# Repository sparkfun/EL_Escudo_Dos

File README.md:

SparkFun EL Escudo Dos
========================================

[*SparkFun EL Escudo Dos (COM-10878)*](https://www.sparkfun.com/products/10878)

The SparkFun EL Escudo Dos is an Arduino shield for controlling up to eight strands of electroluminescent wire. 
EL wire is flexible plastic cord that glows brightly when high-voltage AC is applied to it.
The El Escudo Dos contains circuitry to safely switch high-voltage AC on and off, allowing you to create animated displays or whatever else your imagination can come up with.

Repository Contents
-------------------

* **/Firmware** - Example code 
* **/Hardware** - Eagle design files (.brd, .sch)
* **/Production** - Production panel files (.brd)

Documentation
--------------
* **[Hookup Guide](https://www.sparkfun.com/tutorials/353)** - Basic hookup guide for the EL Escudo Dos.
* **[SparkFun Fritzing repo](https://github.com/sparkfun/Fritzing_Parts)** - Fritzing diagrams for SparkFun products.
* **[SparkFun 3D Model repo](https://github.com/sparkfun/3D_Models)** - 3D models of SparkFun products. 

License Information
-------------------
This product is _**open source**_! 

The **hardware** is released under [Creative Commons ShareAlike 4.0 International](https://creativecommons.org/licenses/by-sa/4.0/).

The **code** is beerware; if you see me (or any other SparkFun employee) at the local, and you've found our code helpful, please buy us a round!

Please use, reuse, and modify these files as you see fit. Please maintain attribution to SparkFun Electronics and release anything derivative under the same license.

Distributed as-is; no warranty is given.

- Your friends at SparkFun.

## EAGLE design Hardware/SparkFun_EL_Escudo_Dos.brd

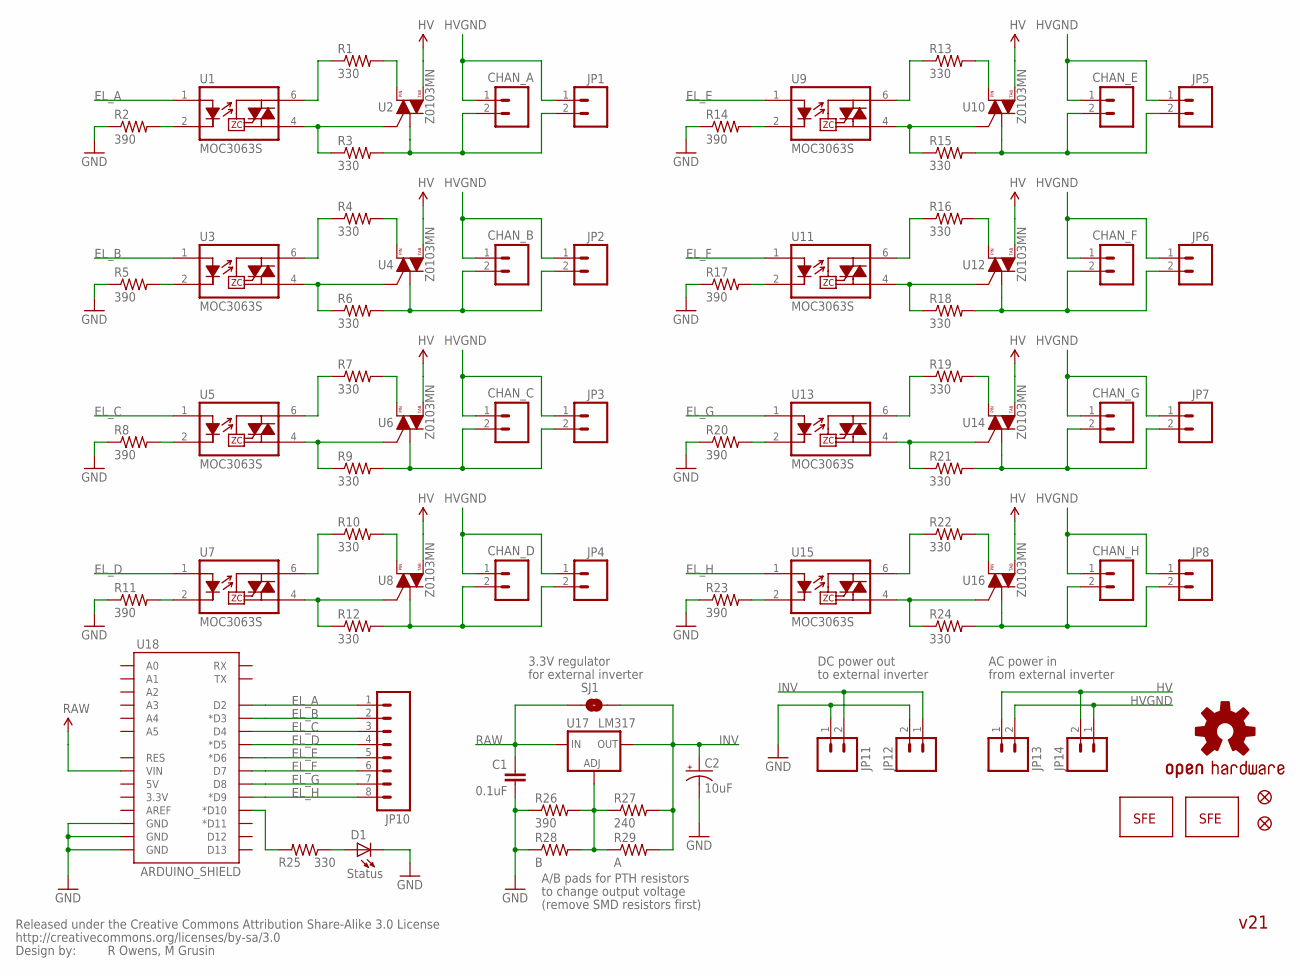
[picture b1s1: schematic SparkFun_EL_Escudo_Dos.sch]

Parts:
C1: 0.1uF; 0603-CAP
C2: 10uF; EIA3216
CHAN_A: M02-JST-2MM-SMT; JST-2-SMD
CHAN_B: M02-JST-2MM-SMT; JST-2-SMD
CHAN_C: M02-JST-2MM-SMT; JST-2-SMD
CHAN_D: M02-JST-2MM-SMT; JST-2-SMD
CHAN_E: M02-JST-2MM-SMT; JST-2-SMD
CHAN_F: M02-JST-2MM-SMT; JST-2-SMD
CHAN_G: M02-JST-2MM-SMT; JST-2-SMD
CHAN_H: M02-JST-2MM-SMT; JST-2-SMD
D1: Status; LED-0603
JP1, JP2, JP3, JP4, JP5, JP6, JP7, JP8, JP12, JP13: M02PTH; 1X02
JP9, JP15: LOGO-SFENEW; SFE-NEW-WEBLOGO
JP10: M081X08; 1X08
JP11, JP14: M02-JST-2MM-SMT; JST-2-SMD
JP16, JP17: FIDUCIALUFIDUCIAL; MICRO-FIDUCIAL
R1, R3, R4, R6, R7, R9, R10, R12, R13, R15, R16, R18, R19, R21, R22, R24, R25: 330; 0603-RES
R2, R5, R8, R11, R14, R17, R20, R23, R26: 390; 0603-RES
R27: 240; 0603-RES
R28: B; AXIAL-0.4
R29: A; AXIAL-0.4
SJ1: SOLDERJUMPERNO; SJ_2S-NO
U1, U3, U5, U7, U9, U11, U13, U15: MOC3063S; DIP8SMD
U2, U4, U6, U8, U10, U12, U14, U16: Z0103MN; SOT223
U17: LM317; V-REG_DPACK
U18: ARDUINO_SHIELD; DUEMILANOVE_SHIELD_NOLABELS
U$4: CREATIVE_COMMONS
U$5: OSHW-LOGOS; OSHW-LOGO-S

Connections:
EL_A: JP10.1, U1.1 (A), U18.D2
EL_B: JP10.2, U3.1 (A), U18.D3 (*D3)
EL_C: JP10.3, U5.1 (A), U18.D4
EL_D: JP10.4, U7.1 (A), U18.D5 (*D5)
EL_E: JP10.5, U9.1 (A), U18.D6 (*D6)
EL_F: JP10.6, U11.1 (A), U18.D7
EL_G: JP10.7, U13.1 (A), U18.D8
EL_H: JP10.8, U15.1 (A), U18.D9 (*D9)
GND: C1.2, C2.C (-), D1.C, JP11.1, JP12.2, R2.1, R5.1, R8.1, R11.1, R14.1, R17.1, R20.1, R23.1, R26.1, R28.P$1 (1), U18.GND@0 (GND), U18.GND@1 (GND), U18.GND@2 (GND)
HV: JP13.1, JP14.2, U2.4 (T2), U4.4 (T2), U6.4 (T2), U8.4 (T2), U10.4 (T2), U12.4 (T2), U14.4 (T2), U16.4 (T2)
HVGND: CHAN_A.1, CHAN_B.1, CHAN_C.1, CHAN_D.1, CHAN_E.1, CHAN_F.1, CHAN_G.1, CHAN_H.1, JP1.1, JP2.1, JP3.1, JP4.1, JP5.1, JP6.1, JP7.1, JP8.1, JP13.2, JP14.1
INV: C2.A (+), JP11.2, JP12.1, R27.2, R29.P$2 (2), SJ1.2, U17.4 (OUT)
unnamed: R2.2, U1.2 (K)
unnamed: R26.2, R27.1, R28.P$2 (2), R29.P$1 (1), U17.1 (ADJ)
unnamed: R1.1, U1.6 (T1)
unnamed: R25.2, U18.D10 (*D10)
unnamed: R6.1, U3.4 (T2), U4.3 (G)
unnamed: R5.2, U3.2 (K)
unnamed: R4.1, U3.6 (T1)
unnamed: CHAN_B.2, JP2.2, R6.2, U4.1 (T1)
unnamed: R1.2, U2.2 (T2)
unnamed: R9.1, U5.4 (T2), U6.3 (G)
unnamed: R8.2, U5.2 (K)
unnamed: R7.1, U5.6 (T1)
unnamed: CHAN_C.2, JP3.2, R9.2, U6.1 (T1)
unnamed: D1.A, R25.1
unnamed: R4.2, U4.2 (T2)
unnamed: R12.1, U7.4 (T2), U8.3 (G)
unnamed: R11.2, U7.2 (K)
unnamed: R10.1, U7.6 (T1)
unnamed: CHAN_D.2, JP4.2, R12.2, U8.1 (T1)
unnamed: R7.2, U6.2 (T2)
unnamed: CHAN_A.2, JP1.2, R3.2, U2.1 (T1)
unnamed: R15.1, U9.4 (T2), U10.3 (G)
unnamed: R14.2, U9.2 (K)
unnamed: R13.1, U9.6 (T1)
unnamed: CHAN_E.2, JP5.2, R15.2, U10.1 (T1)
unnamed: R10.2, U8.2 (T2)
unnamed: R18.1, U11.4 (T2), U12.3 (G)
unnamed: R17.2, U11.2 (K)
unnamed: R16.1, U11.6 (T1)
unnamed: CHAN_F.2, JP6.2, R18.2, U12.1 (T1)
unnamed: R13.2, U10.2 (T2)
unnamed: R21.1, U13.4 (T2), U14.3 (G)
unnamed: R20.2, U13.2 (K)
unnamed: R19.1, U13.6 (T1)
unnamed: CHAN_G.2, JP7.2, R21.2, U14.1 (T1)
unnamed: R16.2, U12.2 (T2)
unnamed: R24.1, U15.4 (T2), U16.3 (G)
unnamed: R23.2, U15.2 (K)
unnamed: R22.1, U15.6 (T1)
unnamed: CHAN_H.2, JP8.2, R24.2, U16.1 (T1)
unnamed: R19.2, U14.2 (T2)
unnamed: R22.2, U16.2 (T2)
unnamed: R3.1, U1.4 (T2), U2.3 (G)
RAW: C1.1, SJ1.1, U17.3 (IN), U18.VIN

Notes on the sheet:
AC power in
from external inverter
DC power out
to external inverter
3.3V regulator
R Owens, M Grusin
for external inverter
A/B pads for PTH resistors
to change output voltage
(remove SMD resistors first)
v21

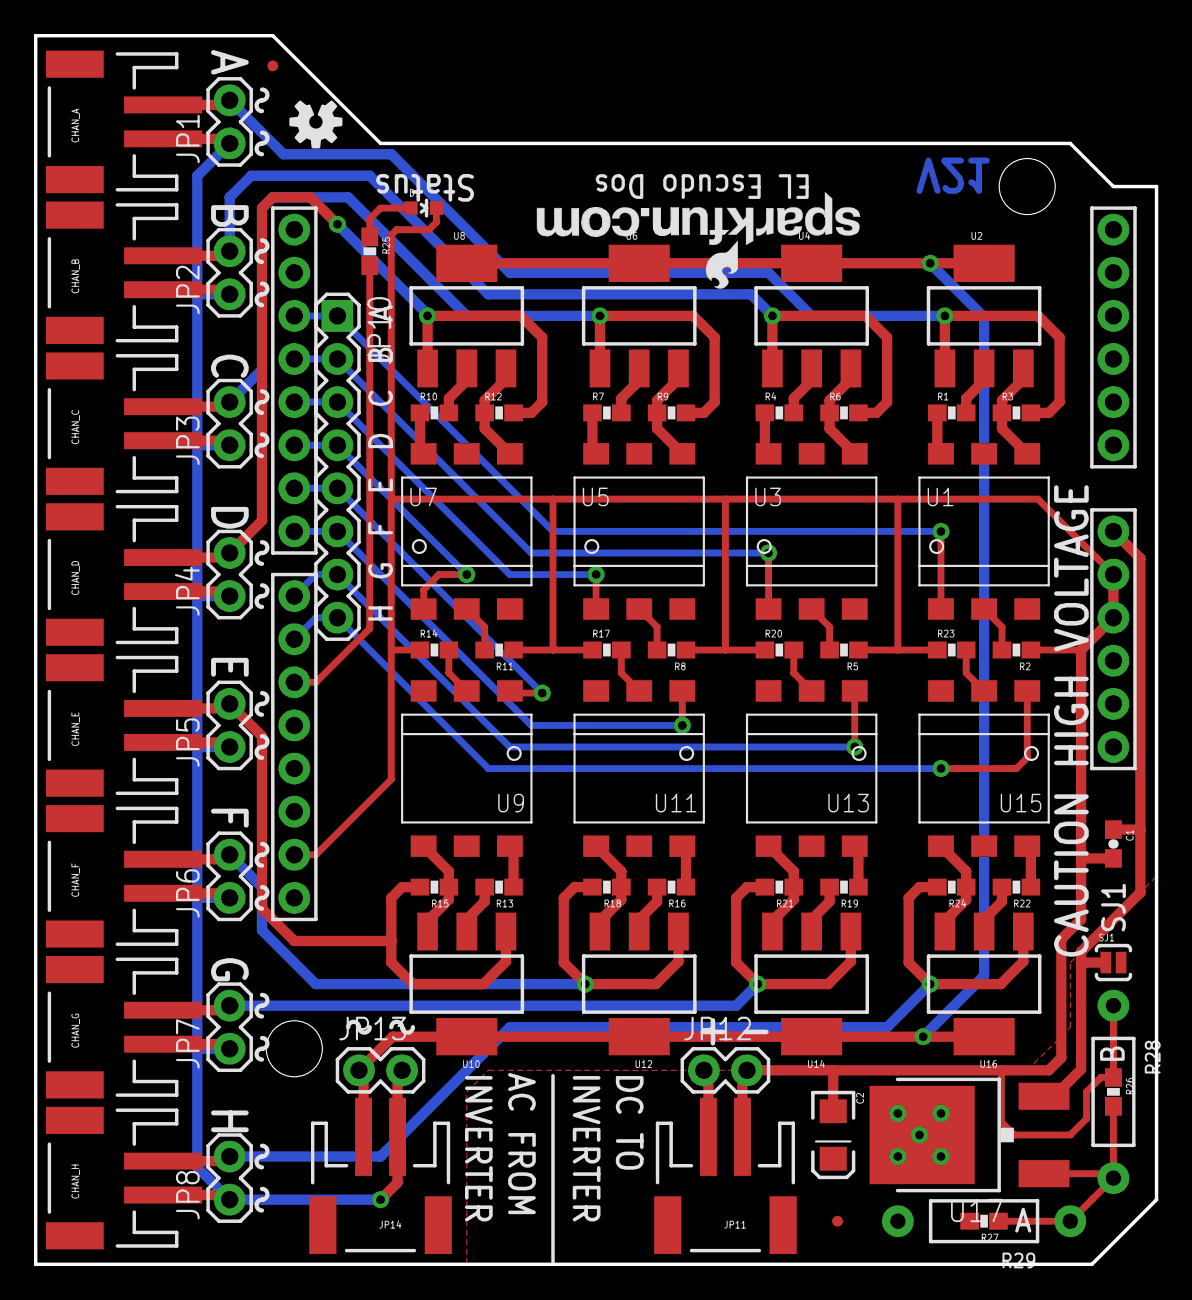
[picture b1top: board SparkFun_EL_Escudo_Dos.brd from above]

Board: 2 copper layers, 66.0 x 72.4 mm, 78 parts (1 on the bottom side), 56 nets.

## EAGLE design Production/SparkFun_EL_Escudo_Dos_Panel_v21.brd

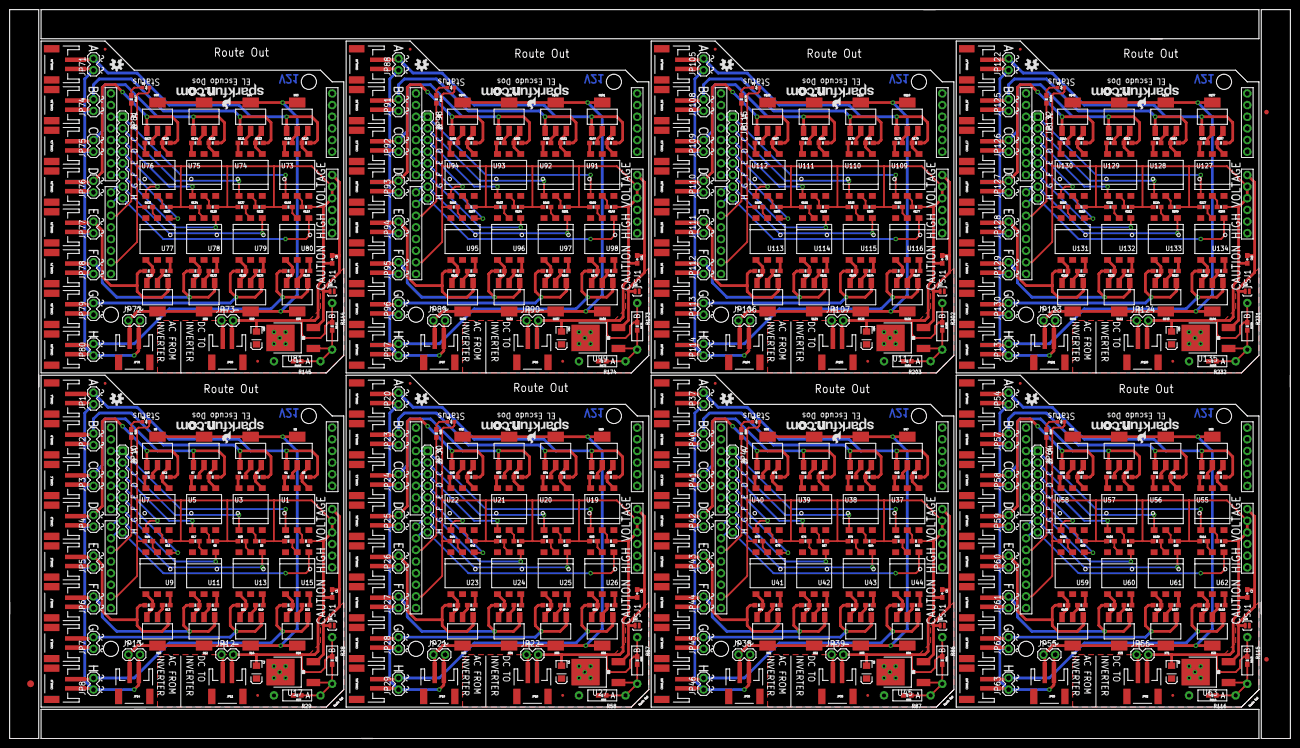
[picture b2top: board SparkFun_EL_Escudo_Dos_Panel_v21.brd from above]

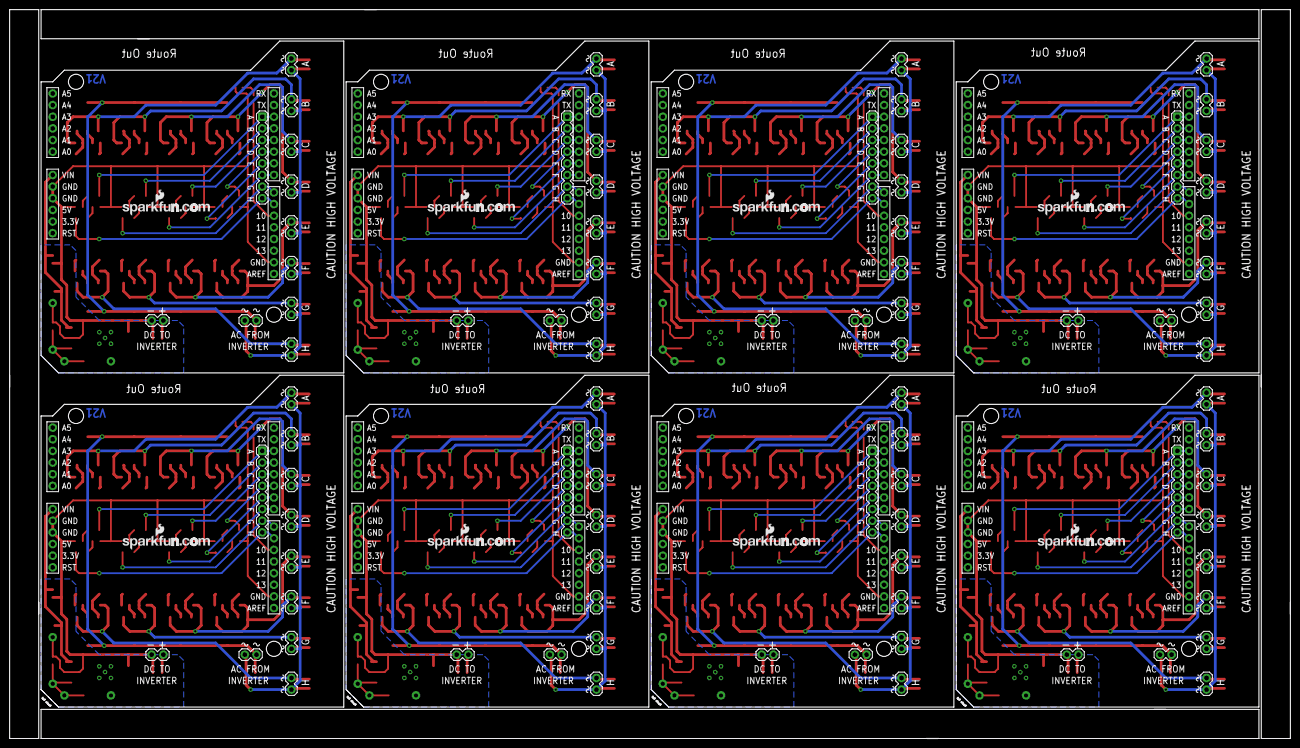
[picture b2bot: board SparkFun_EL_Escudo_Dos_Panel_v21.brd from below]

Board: 2 copper layers, 279.4 x 159.0 mm, 619 parts (8 on the bottom side), 448 nets.

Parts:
C1, C3, C5, C7, C9, C11, C13, C15: 0.1uF; 0603-CAP
C2, C4, C6, C8, C10, C12, C14, C16: 10uF; EIA3216
CHAN_A, CHAN_A1, CHAN_A2, CHAN_A3, CHAN_A4, CHAN_A5, CHAN_A6, CHAN_A7: JST-2-SMD
CHAN_B, CHAN_B1, CHAN_B2, CHAN_B3, CHAN_B4, CHAN_B5, CHAN_B6, CHAN_B7: JST-2-SMD
CHAN_C, CHAN_C1, CHAN_C2, CHAN_C3, CHAN_C4, CHAN_C5, CHAN_C6, CHAN_C7: JST-2-SMD
CHAN_D, CHAN_D1, CHAN_D2, CHAN_D3, CHAN_D4, CHAN_D5, CHAN_D6, CHAN_D7: JST-2-SMD
CHAN_E, CHAN_E1, CHAN_E2, CHAN_E3, CHAN_E4, CHAN_E5, CHAN_E6, CHAN_E7: JST-2-SMD
CHAN_F, CHAN_F1, CHAN_F2, CHAN_F3, CHAN_F4, CHAN_F5, CHAN_F6, CHAN_F7: JST-2-SMD
CHAN_G, CHAN_G1, CHAN_G2, CHAN_G3, CHAN_G4, CHAN_G5, CHAN_G6, CHAN_G7: JST-2-SMD
CHAN_H, CHAN_H1, CHAN_H2, CHAN_H3, CHAN_H4, CHAN_H5, CHAN_H6, CHAN_H7: JST-2-SMD
D1, D2, D3, D4, D5, D6, D7, D8: Status; LED-0603
E$1: FIDUCIAL-1.5X3
E$5, E$6: FIDUCIAL-1X2
JP1, JP2, JP3, JP4, JP5, JP6, JP7, JP8, JP12, JP13, JP20, JP21, JP22, JP23, JP24, JP25, JP26, JP27, JP28, JP29, JP37, JP38, JP39, JP40, JP41, JP42, JP43, JP44, JP45, JP46, JP54, JP55, JP56, JP57, JP58, JP59, JP60, JP61, JP62, JP63, JP71, JP72, JP73, JP74, JP75, JP76, JP77, JP78, JP79, JP80, JP88, JP89, JP90, JP91, JP92, JP93, JP94, JP95, JP96, JP97, JP105, JP106, JP107, JP108, JP109, JP110, JP111, JP112, JP113, JP114, JP122, JP123, JP124, JP125, JP126, JP127, JP128, JP129, JP130, JP131: 1X02
JP9, JP15, JP31, JP32, JP48, JP49, JP65, JP66, JP82, JP83, JP99, JP100, JP116, JP117, JP133, JP134: LOGO-SFENEW; SFE-NEW-WEBLOGO
JP10, JP30, JP47, JP64, JP81, JP98, JP115, JP132: 1X08
JP11, JP14, JP18, JP19, JP35, JP36, JP52, JP53, JP69, JP70, JP86, JP87, JP103, JP104, JP120, JP121: JST-2-SMD
JP16, JP17, JP33, JP34, JP50, JP51, JP67, JP68, JP84, JP85, JP101, JP102, JP118, JP119, JP135, JP136: FIDUCIALUFIDUCIAL; MICRO-FIDUCIAL
R1, R3, R4, R6, R7, R9, R10, R12, R13, R15, R16, R18, R19, R21, R22, R24, R25, R30, R31, R33, R34, R36, R37, R39, R40, R42, R43, R45, R46, R48, R49, R51, R52, R54, R59, R60, R62, R63, R65, R66, R68, R69, R71, R72, R74, R75, R77, R78, R80, R81, R83, R88, R89, R91, R92, R94, R95, R97, R98, R100, R101, R103, R104, R106, R107, R109, R110, R112, R117, R118, R120, R121, R123, R124, R126, R127, R129, R130, R132, R133, R135, R136, R138, R139, R141, R146, R147, R149, R150, R152, R153, R155, R156, R158, R159, R161, R162, R164, R165, R167, R168, R170, R175, R176, R178, R179, R181, R182, R184, R185, R187, R188, R190, R191, R193, R194, R196, R197, R199, R204, R205, R207, R208, R210, R211, R213, R214, R216, R217, R219, R220, R222, R223, R225, R226, R228: 330; 0603-RES
R2, R5, R8, R11, R14, R17, R20, R23, R26, R32, R35, R38, R41, R44, R47, R50, R53, R55, R61, R64, R67, R70, R73, R76, R79, R82, R84, R90, R93, R96, R99, R102, R105, R108, R111, R113, R119, R122, R125, R128, R131, R134, R137, R140, R142, R148, R151, R154, R157, R160, R163, R166, R169, R171, R177, R180, R183, R186, R189, R192, R195, R198, R200, R206, R209, R212, R215, R218, R221, R224, R227, R229: 390; 0603-RES
R27, R56, R85, R114, R143, R172, R201, R230: 240; 0603-RES
R28, R57, R86, R115, R144, R173, R202, R231: B; AXIAL-0.4
R29, R58, R87, R116, R145, R174, R203, R232: A; AXIAL-0.4
SJ1, SJ2, SJ3, SJ4, SJ5, SJ6, SJ7, SJ8: SJ_2S-NO
U1, U3, U5, U7, U9, U11, U13, U15, U19, U20, U21, U22, U23, U24, U25, U26, U37, U38, U39, U40, U41, U42, U43, U44, U55, U56, U57, U58, U59, U60, U61, U62, U73, U74, U75, U76, U77, U78, U79, U80, U91, U92, U93, U94, U95, U96, U97, U98, U109, U110, U111, U112, U113, U114, U115, U116, U127, U128, U129, U130, U131, U132, U133, U134: MOC3063S; DIP8SMD
U2, U4, U6, U8, U10, U12, U14, U16, U29, U30, U31, U32, U33, U34, U35, U36, U47, U48, U49, U50, U51, U52, U53, U54, U65, U66, U67, U68, U69, U70, U71, U72, U83, U84, U85, U86, U87, U88, U89, U90, U101, U102, U103, U104, U105, U106, U107, U108, U119, U120, U121, U122, U123, U124, U125, U126, U137, U138, U139, U140, U141, U142, U143, U144: Z0103MN; SOT223
U17, U27, U45, U63, U81, U99, U117, U135: LM317; V-REG_DPACK
U18, U28, U46, U64, U82, U100, U118, U136: ARDUINO_SHIELD; DUEMILANOVE_SHIELD_NOLABELS
U$1, U$2, U$3, U$4, U$5, U$6, U$7, U$8: OSHW-LOGOS; OSHW-LOGO-S

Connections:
EL_A: JP10.1, U1.1, U18.D2
EL_A1: JP30.1, U19.1, U28.D2
EL_A2: JP47.1, U37.1, U46.D2
EL_A3: JP64.1, U55.1, U64.D2
EL_A4: JP81.1, U73.1, U82.D2
EL_A5: JP98.1, U91.1, U100.D2
EL_A6: JP115.1, U109.1, U118.D2
EL_A7: JP132.1, U127.1, U136.D2
EL_B: JP10.2, U3.1, U18.D3
EL_B1: JP30.2, U20.1, U28.D3
EL_B2: JP47.2, U38.1, U46.D3
EL_B3: JP64.2, U56.1, U64.D3
EL_B4: JP81.2, U74.1, U82.D3
EL_B5: JP98.2, U92.1, U100.D3
EL_B6: JP115.2, U110.1, U118.D3
EL_B7: JP132.2, U128.1, U136.D3
EL_C: JP10.3, U5.1, U18.D4
EL_C1: JP30.3, U21.1, U28.D4
EL_C2: JP47.3, U39.1, U46.D4
EL_C3: JP64.3, U57.1, U64.D4
EL_C4: JP81.3, U75.1, U82.D4
EL_C5: JP98.3, U93.1, U100.D4
EL_C6: JP115.3, U111.1, U118.D4
EL_C7: JP132.3, U129.1, U136.D4
EL_D: JP10.4, U7.1, U18.D5
EL_D1: JP30.4, U22.1, U28.D5
EL_D2: JP47.4, U40.1, U46.D5
EL_D3: JP64.4, U58.1, U64.D5
EL_D4: JP81.4, U76.1, U82.D5
EL_D5: JP98.4, U94.1, U100.D5
EL_D6: JP115.4, U112.1, U118.D5
EL_D7: JP132.4, U130.1, U136.D5
EL_E: JP10.5, U9.1, U18.D6
EL_E1: JP30.5, U23.1, U28.D6
EL_E2: JP47.5, U41.1, U46.D6
EL_E3: JP64.5, U59.1, U64.D6
EL_E4: JP81.5, U77.1, U82.D6
EL_E5: JP98.5, U95.1, U100.D6
EL_E6: JP115.5, U113.1, U118.D6
EL_E7: JP132.5, U131.1, U136.D6
EL_F: JP10.6, U11.1, U18.D7
EL_F1: JP30.6, U24.1, U28.D7
EL_F2: JP47.6, U42.1, U46.D7
EL_F3: JP64.6, U60.1, U64.D7
EL_F4: JP81.6, U78.1, U82.D7
EL_F5: JP98.6, U96.1, U100.D7
EL_F6: JP115.6, U114.1, U118.D7
EL_F7: JP132.6, U132.1, U136.D7
EL_G: JP10.7, U13.1, U18.D8
EL_G1: JP30.7, U25.1, U28.D8
EL_G2: JP47.7, U43.1, U46.D8
EL_G3: JP64.7, U61.1, U64.D8
EL_G4: JP81.7, U79.1, U82.D8
EL_G5: JP98.7, U97.1, U100.D8
EL_G6: JP115.7, U115.1, U118.D8
EL_G7: JP132.7, U133.1, U136.D8
EL_H: JP10.8, U15.1, U18.D9
EL_H1: JP30.8, U26.1, U28.D9
EL_H2: JP47.8, U44.1, U46.D9
EL_H3: JP64.8, U62.1, U64.D9
EL_H4: JP81.8, U80.1, U82.D9
EL_H5: JP98.8, U98.1, U100.D9
EL_H6: JP115.8, U116.1, U118.D9
EL_H7: JP132.8, U134.1, U136.D9
GND: C1.2, C2.C, D1.C, JP11.1, JP12.2, R2.1, R5.1, R8.1, R11.1, R14.1, R17.1, R20.1, R23.1, R26.1, R28.P$1, U18.GND@0, U18.GND@1, U18.GND@2
GND1: C3.2, C4.C, D2.C, JP18.1, JP22.2, R32.1, R35.1, R38.1, R41.1, R44.1, R47.1, R50.1, R53.1, R55.1, R57.P$1, U28.GND@0, U28.GND@1, U28.GND@2
GND2: C5.2, C6.C, D3.C, JP35.1, JP39.2, R61.1, R64.1, R67.1, R70.1, R73.1, R76.1, R79.1, R82.1, R84.1, R86.P$1, U46.GND@0, U46.GND@1, U46.GND@2
GND3: C7.2, C8.C, D4.C, JP52.1, JP56.2, R90.1, R93.1, R96.1, R99.1, R102.1, R105.1, R108.1, R111.1, R113.1, R115.P$1, U64.GND@0, U64.GND@1, U64.GND@2
GND4: C9.2, C10.C, D5.C, JP69.1, JP73.2, R119.1, R122.1, R125.1, R128.1, R131.1, R134.1, R137.1, R140.1, R142.1, R144.P$1, U82.GND@0, U82.GND@1, U82.GND@2
GND5: C11.2, C12.C, D6.C, JP86.1, JP90.2, R148.1, R151.1, R154.1, R157.1, R160.1, R163.1, R166.1, R169.1, R171.1, R173.P$1, U100.GND@0, U100.GND@1, U100.GND@2
GND6: C13.2, C14.C, D7.C, JP103.1, JP107.2, R177.1, R180.1, R183.1, R186.1, R189.1, R192.1, R195.1, R198.1, R200.1, R202.P$1, U118.GND@0, U118.GND@1, U118.GND@2
GND7: C15.2, C16.C, D8.C, JP120.1, JP124.2, R206.1, R209.1, R212.1, R215.1, R218.1, R221.1, R224.1, R227.1, R229.1, R231.P$1, U136.GND@0, U136.GND@1, U136.GND@2
HV: JP13.1, JP14.2, U2.4, U4.4, U6.4, U8.4, U10.4, U12.4, U14.4, U16.4
HV1: JP19.2, JP21.1, U29.4, U30.4, U31.4, U32.4, U33.4, U34.4, U35.4, U36.4
HV2: JP36.2, JP38.1, U47.4, U48.4, U49.4, U50.4, U51.4, U52.4, U53.4, U54.4
HV3: JP53.2, JP55.1, U65.4, U66.4, U67.4, U68.4, U69.4, U70.4, U71.4, U72.4
HV4: JP70.2, JP72.1, U83.4, U84.4, U85.4, U86.4, U87.4, U88.4, U89.4, U90.4
HV5: JP87.2, JP89.1, U101.4, U102.4, U103.4, U104.4, U105.4, U106.4, U107.4, U108.4
HV6: JP104.2, JP106.1, U119.4, U120.4, U121.4, U122.4, U123.4, U124.4, U125.4, U126.4
HV7: JP121.2, JP123.1, U137.4, U138.4, U139.4, U140.4, U141.4, U142.4, U143.4, U144.4
HVGND: CHAN_A.1, CHAN_B.1, CHAN_C.1, CHAN_D.1, CHAN_E.1, CHAN_F.1, CHAN_G.1, CHAN_H.1, JP1.1, JP2.1, JP3.1, JP4.1, JP5.1, JP6.1, JP7.1, JP8.1, JP13.2, JP14.1
HVGND1: CHAN_A1.1, CHAN_B1.1, CHAN_C1.1, CHAN_D1.1, CHAN_E1.1, CHAN_F1.1, CHAN_G1.1, CHAN_H1.1, JP19.1, JP20.1, JP21.2, JP23.1, JP24.1, JP25.1, JP26.1, JP27.1, JP28.1, JP29.1
HVGND2: CHAN_A2.1, CHAN_B2.1, CHAN_C2.1, CHAN_D2.1, CHAN_E2.1, CHAN_F2.1, CHAN_G2.1, CHAN_H2.1, JP36.1, JP37.1, JP38.2, JP40.1, JP41.1, JP42.1, JP43.1, JP44.1, JP45.1, JP46.1
HVGND3: CHAN_A3.1, CHAN_B3.1, CHAN_C3.1, CHAN_D3.1, CHAN_E3.1, CHAN_F3.1, CHAN_G3.1, CHAN_H3.1, JP53.1, JP54.1, JP55.2, JP57.1, JP58.1, JP59.1, JP60.1, JP61.1, JP62.1, JP63.1
HVGND4: CHAN_A4.1, CHAN_B4.1, CHAN_C4.1, CHAN_D4.1, CHAN_E4.1, CHAN_F4.1, CHAN_G4.1, CHAN_H4.1, JP70.1, JP71.1, JP72.2, JP74.1, JP75.1, JP76.1, JP77.1, JP78.1, JP79.1, JP80.1
HVGND5: CHAN_A5.1, CHAN_B5.1, CHAN_C5.1, CHAN_D5.1, CHAN_E5.1, CHAN_F5.1, CHAN_G5.1, CHAN_H5.1, JP87.1, JP88.1, JP89.2, JP91.1, JP92.1, JP93.1, JP94.1, JP95.1, JP96.1, JP97.1
HVGND6: CHAN_A6.1, CHAN_B6.1, CHAN_C6.1, CHAN_D6.1, CHAN_E6.1, CHAN_F6.1, CHAN_G6.1, CHAN_H6.1, JP104.1, JP105.1, JP106.2, JP108.1, JP109.1, JP110.1, JP111.1, JP112.1, JP113.1, JP114.1
HVGND7: CHAN_A7.1, CHAN_B7.1, CHAN_C7.1, CHAN_D7.1, CHAN_E7.1, CHAN_F7.1, CHAN_G7.1, CHAN_H7.1, JP121.1, JP122.1, JP123.2, JP125.1, JP126.1, JP127.1, JP128.1, JP129.1, JP130.1, JP131.1
INV: C2.A, JP11.2, JP12.1, R27.2, R29.P$2, SJ1.2, U17.4
INV1: C4.A, JP18.2, JP22.1, R56.2, R58.P$2, SJ2.2, U27.4
INV2: C6.A, JP35.2, JP39.1, R85.2, R87.P$2, SJ3.2, U45.4
INV3: C8.A, JP52.2, JP56.1, R114.2, R116.P$2, SJ4.2, U63.4
INV4: C10.A, JP69.2, JP73.1, R143.2, R145.P$2, SJ5.2, U81.4
INV5: C12.A, JP86.2, JP90.1, R172.2, R174.P$2, SJ6.2, U99.4
INV6: C14.A, JP103.2, JP107.1, R201.2, R203.P$2, SJ7.2, U117.4
INV7: C16.A, JP120.2, JP124.1, R230.2, R232.P$2, SJ8.2, U135.4
unnamed: R2.2, U1.2
unnamed: R26.2, R27.1, R28.P$2, R29.P$1, U17.1
unnamed: R1.1, U1.6
unnamed: R25.2, U18.D10
unnamed: R6.1, U3.4, U4.3
unnamed: R5.2, U3.2
unnamed: R4.1, U3.6
unnamed: CHAN_B.2, JP2.2, R6.2, U4.1
unnamed: R1.2, U2.2
unnamed: R9.1, U5.4, U6.3
unnamed: R8.2, U5.2
unnamed: R7.1, U5.6
unnamed: CHAN_C.2, JP3.2, R9.2, U6.1
unnamed: D1.A, R25.1
unnamed: R4.2, U4.2
unnamed: R12.1, U7.4, U8.3
unnamed: R11.2, U7.2
unnamed: R10.1, U7.6
unnamed: CHAN_D.2, JP4.2, R12.2, U8.1
unnamed: R7.2, U6.2
unnamed: CHAN_A.2, JP1.2, R3.2, U2.1
unnamed: R15.1, U9.4, U10.3
unnamed: R14.2, U9.2
unnamed: R13.1, U9.6
unnamed: CHAN_E.2, JP5.2, R15.2, U10.1
unnamed: R10.2, U8.2
unnamed: R18.1, U11.4, U12.3
unnamed: R17.2, U11.2
unnamed: R16.1, U11.6
unnamed: CHAN_F.2, JP6.2, R18.2, U12.1
unnamed: R13.2, U10.2
unnamed: R21.1, U13.4, U14.3
unnamed: R20.2, U13.2
unnamed: R19.1, U13.6
unnamed: CHAN_G.2, JP7.2, R21.2, U14.1
unnamed: R16.2, U12.2
unnamed: R24.1, U15.4, U16.3
unnamed: R23.2, U15.2
unnamed: R22.1, U15.6
unnamed: CHAN_H.2, JP8.2, R24.2, U16.1
unnamed: R19.2, U14.2
unnamed: R22.2, U16.2
unnamed: D2.A, R30.1
unnamed: R33.1, U19.4, U29.3
unnamed: R32.2, U19.2
unnamed: R31.1, U19.6
unnamed: CHAN_A1.2, JP20.2, R33.2, U29.1
unnamed: R36.1, U20.4, U30.3
unnamed: R35.2, U20.2
unnamed: R34.1, U20.6
unnamed: CHAN_B1.2, JP23.2, R36.2, U30.1
unnamed: R39.1, U21.4, U31.3
unnamed: R38.2, U21.2
unnamed: R37.1, U21.6
unnamed: CHAN_C1.2, JP24.2, R39.2, U31.1
unnamed: R42.1, U22.4, U32.3
unnamed: R41.2, U22.2
unnamed: R40.1, U22.6
unnamed: CHAN_D1.2, JP25.2, R42.2, U32.1
unnamed: R45.1, U23.4, U33.3
unnamed: R44.2, U23.2
unnamed: R43.1, U23.6
unnamed: CHAN_E1.2, JP26.2, R45.2, U33.1
unnamed: R48.1, U24.4, U34.3
unnamed: R47.2, U24.2
unnamed: R46.1, U24.6
unnamed: CHAN_F1.2, JP27.2, R48.2, U34.1
unnamed: R51.1, U25.4, U35.3
unnamed: R50.2, U25.2
unnamed: R49.1, U25.6
unnamed: CHAN_G1.2, JP28.2, R51.2, U35.1
unnamed: R54.1, U26.4, U36.3
unnamed: R53.2, U26.2
unnamed: R52.1, U26.6
unnamed: CHAN_H1.2, JP29.2, R54.2, U36.1
unnamed: R55.2, R56.1, R57.P$2, R58.P$1, U27.1
unnamed: R31.2, U29.2
unnamed: R34.2, U30.2
unnamed: R37.2, U31.2
unnamed: R40.2, U32.2
unnamed: R43.2, U33.2
unnamed: R46.2, U34.2
unnamed: R49.2, U35.2
unnamed: R52.2, U36.2
unnamed: R30.2, U28.D10
unnamed: D3.A, R59.1
unnamed: R62.1, U37.4, U47.3
unnamed: R61.2, U37.2
unnamed: R60.1, U37.6
unnamed: CHAN_A2.2, JP37.2, R62.2, U47.1
unnamed: R65.1, U38.4, U48.3
unnamed: R64.2, U38.2
unnamed: R63.1, U38.6
unnamed: CHAN_B2.2, JP40.2, R65.2, U48.1
unnamed: R68.1, U39.4, U49.3
unnamed: R67.2, U39.2
unnamed: R66.1, U39.6
unnamed: CHAN_C2.2, JP41.2, R68.2, U49.1
unnamed: R71.1, U40.4, U50.3
unnamed: R70.2, U40.2
unnamed: R69.1, U40.6
unnamed: CHAN_D2.2, JP42.2, R71.2, U50.1
unnamed: R74.1, U41.4, U51.3
unnamed: R73.2, U41.2
unnamed: R72.1, U41.6
unnamed: CHAN_E2.2, JP43.2, R74.2, U51.1
unnamed: R77.1, U42.4, U52.3
unnamed: R76.2, U42.2
unnamed: R75.1, U42.6
unnamed: CHAN_F2.2, JP44.2, R77.2, U52.1
unnamed: R80.1, U43.4, U53.3
unnamed: R79.2, U43.2
unnamed: R78.1, U43.6
unnamed: CHAN_G2.2, JP45.2, R80.2, U53.1
unnamed: R83.1, U44.4, U54.3
unnamed: R82.2, U44.2
unnamed: R3.1, U1.4, U2.3
unnamed: R81.1, U44.6
unnamed: CHAN_H2.2, JP46.2, R83.2, U54.1
unnamed: R84.2, R85.1, R86.P$2, R87.P$1, U45.1
unnamed: R60.2, U47.2
unnamed: R63.2, U48.2
unnamed: R66.2, U49.2
unnamed: R69.2, U50.2
unnamed: R72.2, U51.2
unnamed: R75.2, U52.2
unnamed: R78.2, U53.2
unnamed: R81.2, U54.2
unnamed: R59.2, U46.D10
unnamed: D4.A, R88.1
unnamed: R91.1, U55.4, U65.3
unnamed: R90.2, U55.2
unnamed: R89.1, U55.6
unnamed: CHAN_A3.2, JP54.2, R91.2, U65.1
unnamed: R94.1, U56.4, U66.3
unnamed: R93.2, U56.2
unnamed: R92.1, U56.6
unnamed: CHAN_B3.2, JP57.2, R94.2, U66.1
unnamed: R97.1, U57.4, U67.3
unnamed: R96.2, U57.2
unnamed: R95.1, U57.6
unnamed: CHAN_C3.2, JP58.2, R97.2, U67.1
unnamed: R100.1, U58.4, U68.3
unnamed: R99.2, U58.2
unnamed: R98.1, U58.6
unnamed: CHAN_D3.2, JP59.2, R100.2, U68.1
unnamed: R103.1, U59.4, U69.3
unnamed: R102.2, U59.2
unnamed: R101.1, U59.6
unnamed: CHAN_E3.2, JP60.2, R103.2, U69.1
unnamed: R106.1, U60.4, U70.3
unnamed: R105.2, U60.2
unnamed: R104.1, U60.6
unnamed: CHAN_F3.2, JP61.2, R106.2, U70.1
unnamed: R109.1, U61.4, U71.3
unnamed: R108.2, U61.2
unnamed: R107.1, U61.6
unnamed: CHAN_G3.2, JP62.2, R109.2, U71.1
unnamed: R112.1, U62.4, U72.3
unnamed: R111.2, U62.2
unnamed: R110.1, U62.6
unnamed: CHAN_H3.2, JP63.2, R112.2, U72.1
unnamed: R113.2, R114.1, R115.P$2, R116.P$1, U63.1
unnamed: R89.2, U65.2
unnamed: R92.2, U66.2
unnamed: R95.2, U67.2
unnamed: R98.2, U68.2
unnamed: R101.2, U69.2
unnamed: R104.2, U70.2
unnamed: R107.2, U71.2
unnamed: R110.2, U72.2
unnamed: R88.2, U64.D10
unnamed: D5.A, R117.1
unnamed: R120.1, U73.4, U83.3
unnamed: R119.2, U73.2
unnamed: R118.1, U73.6
unnamed: CHAN_A4.2, JP71.2, R120.2, U83.1
unnamed: R123.1, U74.4, U84.3
unnamed: R122.2, U74.2
unnamed: R121.1, U74.6
unnamed: CHAN_B4.2, JP74.2, R123.2, U84.1
unnamed: R126.1, U75.4, U85.3
unnamed: R125.2, U75.2
unnamed: R124.1, U75.6
unnamed: CHAN_C4.2, JP75.2, R126.2, U85.1
unnamed: R129.1, U76.4, U86.3
unnamed: R128.2, U76.2
unnamed: R127.1, U76.6
unnamed: CHAN_D4.2, JP76.2, R129.2, U86.1
unnamed: R132.1, U77.4, U87.3
unnamed: R131.2, U77.2
unnamed: R130.1, U77.6
unnamed: CHAN_E4.2, JP77.2, R132.2, U87.1
unnamed: R135.1, U78.4, U88.3
unnamed: R134.2, U78.2
unnamed: R133.1, U78.6
unnamed: CHAN_F4.2, JP78.2, R135.2, U88.1
unnamed: R138.1, U79.4, U89.3
unnamed: R137.2, U79.2
unnamed: R136.1, U79.6
unnamed: CHAN_G4.2, JP79.2, R138.2, U89.1
unnamed: R141.1, U80.4, U90.3
unnamed: R140.2, U80.2
unnamed: R139.1, U80.6
unnamed: CHAN_H4.2, JP80.2, R141.2, U90.1
unnamed: R142.2, R143.1, R144.P$2, R145.P$1, U81.1
unnamed: R118.2, U83.2
unnamed: R121.2, U84.2
unnamed: R124.2, U85.2
unnamed: R127.2, U86.2
unnamed: R130.2, U87.2
unnamed: R133.2, U88.2
unnamed: R136.2, U89.2
unnamed: R139.2, U90.2
unnamed: R117.2, U82.D10
unnamed: D6.A, R146.1
unnamed: R149.1, U91.4, U101.3
unnamed: R148.2, U91.2
unnamed: R147.1, U91.6
unnamed: CHAN_A5.2, JP88.2, R149.2, U101.1
unnamed: R152.1, U92.4, U102.3
unnamed: R151.2, U92.2
unnamed: R150.1, U92.6
unnamed: CHAN_B5.2, JP91.2, R152.2, U102.1
unnamed: R155.1, U93.4, U103.3
unnamed: R154.2, U93.2
unnamed: R153.1, U93.6
unnamed: CHAN_C5.2, JP92.2, R155.2, U103.1
unnamed: R158.1, U94.4, U104.3
unnamed: R157.2, U94.2
unnamed: R156.1, U94.6
unnamed: CHAN_D5.2, JP93.2, R158.2, U104.1
unnamed: R161.1, U95.4, U105.3
unnamed: R160.2, U95.2
unnamed: R159.1, U95.6
unnamed: CHAN_E5.2, JP94.2, R161.2, U105.1
unnamed: R164.1, U96.4, U106.3
unnamed: R163.2, U96.2
unnamed: R162.1, U96.6
unnamed: CHAN_F5.2, JP95.2, R164.2, U106.1
unnamed: R167.1, U97.4, U107.3
unnamed: R166.2, U97.2
unnamed: R165.1, U97.6
unnamed: CHAN_G5.2, JP96.2, R167.2, U107.1
unnamed: R170.1, U98.4, U108.3
unnamed: R169.2, U98.2
unnamed: R168.1, U98.6
unnamed: CHAN_H5.2, JP97.2, R170.2, U108.1
unnamed: R171.2, R172.1, R173.P$2, R174.P$1, U99.1
unnamed: R147.2, U101.2
unnamed: R150.2, U102.2
unnamed: R153.2, U103.2
unnamed: R156.2, U104.2
unnamed: R159.2, U105.2
unnamed: R162.2, U106.2
unnamed: R165.2, U107.2
unnamed: R168.2, U108.2
unnamed: R146.2, U100.D10
unnamed: D7.A, R175.1
unnamed: R178.1, U109.4, U119.3
unnamed: R177.2, U109.2
unnamed: R176.1, U109.6
unnamed: CHAN_A6.2, JP105.2, R178.2, U119.1
unnamed: R181.1, U110.4, U120.3
unnamed: R180.2, U110.2
unnamed: R179.1, U110.6
unnamed: CHAN_B6.2, JP108.2, R181.2, U120.1
unnamed: R184.1, U111.4, U121.3
unnamed: R183.2, U111.2
unnamed: R182.1, U111.6
unnamed: CHAN_C6.2, JP109.2, R184.2, U121.1
unnamed: R187.1, U112.4, U122.3
unnamed: R186.2, U112.2
unnamed: R185.1, U112.6
unnamed: CHAN_D6.2, JP110.2, R187.2, U122.1
unnamed: R190.1, U113.4, U123.3
unnamed: R189.2, U113.2
unnamed: R188.1, U113.6
unnamed: CHAN_E6.2, JP111.2, R190.2, U123.1
unnamed: R193.1, U114.4, U124.3
unnamed: R192.2, U114.2
unnamed: R191.1, U114.6
unnamed: CHAN_F6.2, JP112.2, R193.2, U124.1
unnamed: R196.1, U115.4, U125.3
unnamed: R195.2, U115.2
unnamed: R194.1, U115.6
unnamed: CHAN_G6.2, JP113.2, R196.2, U125.1
unnamed: R199.1, U116.4, U126.3
unnamed: R198.2, U116.2
unnamed: R197.1, U116.6
unnamed: CHAN_H6.2, JP114.2, R199.2, U126.1
unnamed: R200.2, R201.1, R202.P$2, R203.P$1, U117.1
unnamed: R176.2, U119.2
unnamed: R179.2, U120.2
unnamed: R182.2, U121.2
unnamed: R185.2, U122.2
unnamed: R188.2, U123.2
unnamed: R191.2, U124.2
unnamed: R194.2, U125.2
unnamed: R197.2, U126.2
unnamed: R175.2, U118.D10
unnamed: D8.A, R204.1
unnamed: R207.1, U127.4, U137.3
unnamed: R206.2, U127.2
unnamed: R205.1, U127.6
unnamed: CHAN_A7.2, JP122.2, R207.2, U137.1
unnamed: R210.1, U128.4, U138.3
unnamed: R209.2, U128.2
unnamed: R208.1, U128.6
unnamed: CHAN_B7.2, JP125.2, R210.2, U138.1
unnamed: R213.1, U129.4, U139.3
unnamed: R212.2, U129.2
unnamed: R211.1, U129.6
unnamed: CHAN_C7.2, JP126.2, R213.2, U139.1
unnamed: R216.1, U130.4, U140.3
unnamed: R215.2, U130.2
unnamed: R214.1, U130.6
unnamed: CHAN_D7.2, JP127.2, R216.2, U140.1
unnamed: R219.1, U131.4, U141.3
unnamed: R218.2, U131.2
unnamed: R217.1, U131.6
unnamed: CHAN_E7.2, JP128.2, R219.2, U141.1
unnamed: R222.1, U132.4, U142.3
unnamed: R221.2, U132.2
unnamed: R220.1, U132.6
unnamed: CHAN_F7.2, JP129.2, R222.2, U142.1
unnamed: R225.1, U133.4, U143.3
unnamed: R224.2, U133.2
unnamed: R223.1, U133.6
unnamed: CHAN_G7.2, JP130.2, R225.2, U143.1
unnamed: R228.1, U134.4, U144.3
unnamed: R227.2, U134.2
unnamed: R226.1, U134.6
unnamed: CHAN_H7.2, JP131.2, R228.2, U144.1
unnamed: R229.2, R230.1, R231.P$2, R232.P$1, U135.1
unnamed: R205.2, U137.2
unnamed: R208.2, U138.2
unnamed: R211.2, U139.2
unnamed: R214.2, U140.2
unnamed: R217.2, U141.2
unnamed: R220.2, U142.2
unnamed: R223.2, U143.2
unnamed: R226.2, U144.2
unnamed: R204.2, U136.D10
RAW: C1.1, SJ1.1, U17.3, U18.VIN
RAW1: C3.1, SJ2.1, U27.3, U28.VIN
RAW2: C5.1, SJ3.1, U45.3, U46.VIN
RAW3: C7.1, SJ4.1, U63.3, U64.VIN
RAW4: C9.1, SJ5.1, U81.3, U82.VIN
RAW5: C11.1, SJ6.1, U99.3, U100.VIN
RAW6: C13.1, SJ7.1, U117.3, U118.VIN
RAW7: C15.1, SJ8.1, U135.3, U136.VIN

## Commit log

2015-05-06 Adding hardware files, readme, example sketch
2015-11-12 created new v21 panel

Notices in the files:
parts and their libraries:
SparkFun: Released under the Creative Commons Attribution Share-Alike 3.0 License
SparkFun: http://creativecommons.org/licenses/by-sa/3.0
SparkFun-Aesthetics: Licensing: CC v3.0 Share-Alike You are welcome to use this library for commercial purposes.
